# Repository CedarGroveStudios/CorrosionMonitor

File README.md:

# Corrosion_Monitor
 A CircuitPython and IoT version of the classic Workshop Corrosion Detector

Uses __CedarGroveStudios/Unit_Converter__ custom CircuitPython library.

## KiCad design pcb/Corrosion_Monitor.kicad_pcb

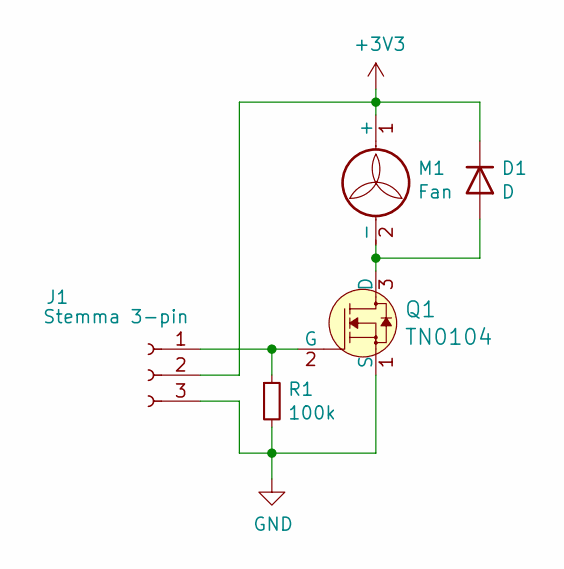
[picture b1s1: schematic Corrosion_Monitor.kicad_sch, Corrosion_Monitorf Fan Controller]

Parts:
D1: D; D_T-1_P2.54mm_Vertical_KathodeUp
J1: Stemma 3-pin; PinHeader_1x03_P2.54mm_Vertical
M1: Fan; PinHeader_1x02_P2.54mm_Vertical
Q1: TN0104; TO-92S; MPN 2N7000; Digi-Key_PN 2N7000FS-ND
R1: 100k; R_Axial_DIN0204_L3.6mm_D1.6mm_P2.54mm_Vertical

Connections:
+3V3: D1.1 (K), J1.2, M1.1 (+)
GND: J1.3, Q1.1 (S), R1.2
unnamed: D1.2 (A), M1.2 (-), Q1.3 (D)
unnamed: J1.1, Q1.2 (G), R1.1

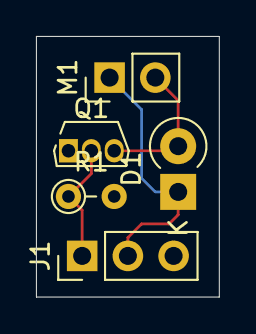
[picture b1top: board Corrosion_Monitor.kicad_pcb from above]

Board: 2 copper layers, 10.2 x 14.5 mm, 5 parts (0 on the bottom side), 4 nets.

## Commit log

2022-07-01 initial repo load
2022-07-06 update with improved gesture control; improved docs
2022-07-07 increase light sensor averaging to improve gesture detection range
2022-07-07 update gesture logic; recalibrate background light calibration after timeout and once per minute
2022-07-07 add clock tick to on-board neopixel
2022-07-08 improve ambient light detection; upgrade to CircuitPython 7.3.1
2022-07-08 Update LICENSE
2022-07-12 update docs; add gesture detector example code
2022-07-12 update gesture detection example
2022-07-12 refactor gesture detection example code
2022-07-13 improve light sensor measurement stability for light flicker
2022-07-17 incorporate new ShadowDetector class
